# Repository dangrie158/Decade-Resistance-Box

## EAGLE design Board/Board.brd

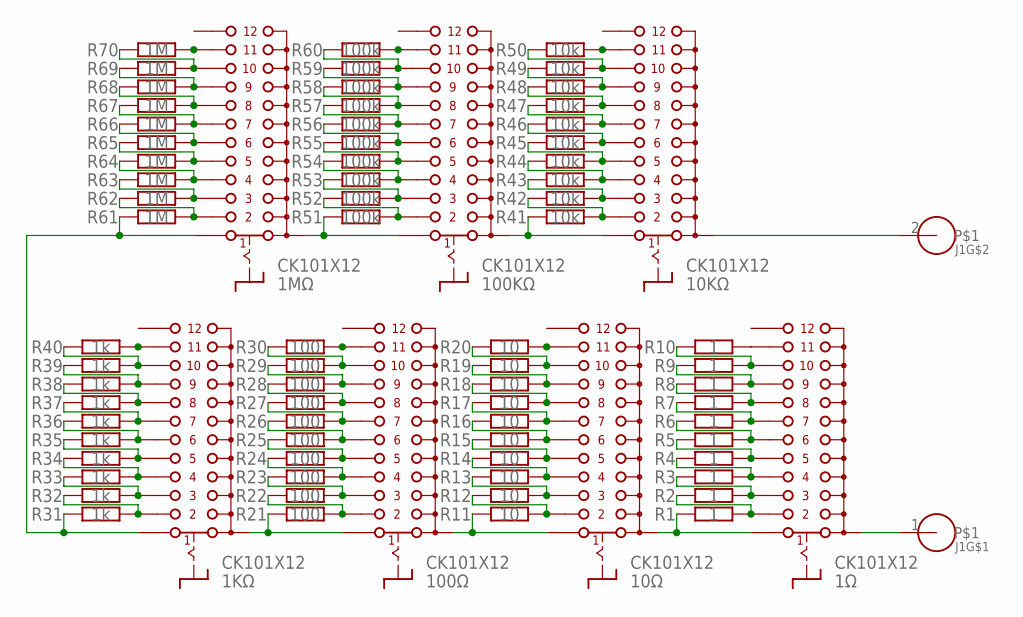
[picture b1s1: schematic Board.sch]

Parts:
1KΩ, 1MΩ, 1Ω, 10KΩ, 10Ω, 100KΩ, 100Ω: CK101X12
J1: MOLEX-1X2; MOLEX-1X2_LOCK
R1, R2, R3, R4, R5, R6, R7, R8, R9, R10: 1; 0207/2V
R11, R12, R13, R14, R15, R16, R17, R18, R19, R20: 10; 0207/2V
R21, R22, R23, R24, R25, R26, R27, R28, R29, R30: 100; 0207/2V
R31, R32, R33, R34, R35, R36, R37, R38, R39, R40: 1k; 0207/2V
R41, R42, R43, R44, R45, R46, R47, R48, R49, R50: 10k; 0207/2V
R51, R52, R53, R54, R55, R56, R57, R58, R59, R60: 100k; 0207/2V
R61, R62, R63, R64, R65, R66, R67, R68, R69, R70: 1M; 0207/2V

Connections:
unnamed: 1Ω.2, R1.2, R2.1
unnamed: 10Ω.2, R11.2, R12.1
unnamed: 10Ω.1, 100Ω.A, R11.1
unnamed: 10Ω.3, R12.2, R13.1
unnamed: 10Ω.4, R13.2, R14.1
unnamed: 10Ω.5, R14.2, R15.1
unnamed: 10Ω.6, R15.2, R16.1
unnamed: 10Ω.7, R16.2, R17.1
unnamed: 10Ω.8, R17.2, R18.1
unnamed: 10Ω.9, R18.2, R19.1
unnamed: 1KΩ.10, R39.2, R40.1
unnamed: 1Ω.3, R2.2, R3.1
unnamed: 1Ω.4, R3.2, R4.1
unnamed: 1Ω.5, R4.2, R5.1
unnamed: 1Ω.6, R5.2, R6.1
unnamed: 10Ω.10, R19.2, R20.1
unnamed: 1Ω.7, R6.2, R7.1
unnamed: 1Ω.8, R7.2, R8.1
unnamed: 1Ω.9, R8.2, R9.1
unnamed: 1Ω.10, R9.2, R10.1
unnamed: 1Ω.11, R10.2
unnamed: 10Ω.11, R20.2
unnamed: 100Ω.2, R21.2, R22.1
unnamed: 10KΩ.1, 100KΩ.A, R41.1
unnamed: 100Ω.3, R22.2, R23.1
unnamed: 100Ω.4, R23.2, R24.1
unnamed: 100Ω.5, R24.2, R25.1
unnamed: 100Ω.6, R25.2, R26.1
unnamed: 100Ω.7, R26.2, R27.1
unnamed: 100Ω.8, R27.2, R28.1
unnamed: 100Ω.9, R28.2, R29.1
unnamed: 100Ω.10, R29.2, R30.1
unnamed: 100Ω.11, R30.2
unnamed: 1KΩ.2, R31.2, R32.1
unnamed: 1Ω.1, 10Ω.A, R1.1
unnamed: 1KΩ.3, R32.2, R33.1
unnamed: 1KΩ.4, R33.2, R34.1
unnamed: 1KΩ.5, R34.2, R35.1
unnamed: 1KΩ.6, R35.2, R36.1
unnamed: 1KΩ.7, R36.2, R37.1
unnamed: 1KΩ.8, R37.2, R38.1
unnamed: 1KΩ.9, R38.2, R39.1
unnamed: 1KΩ.1, 1MΩ.1, R31.1, R61.1
unnamed: 1KΩ.11, R40.2
unnamed: 10KΩ.2, R41.2, R42.1
unnamed: 10KΩ.A, J1.2
unnamed: 10KΩ.3, R42.2, R43.1
unnamed: 10KΩ.4, R43.2, R44.1
unnamed: 10KΩ.5, R44.2, R45.1
unnamed: 10KΩ.6, R45.2, R46.1
unnamed: 10KΩ.7, R46.2, R47.1
unnamed: 10KΩ.8, R47.2, R48.1
unnamed: 10KΩ.9, R48.2, R49.1
unnamed: 10KΩ.10, R49.2, R50.1
unnamed: 10KΩ.11, R50.2
unnamed: 100KΩ.2, R51.2, R52.1
unnamed: 1MΩ.A, 100KΩ.1, R51.1
unnamed: 100KΩ.3, R52.2, R53.1
unnamed: 100KΩ.4, R53.2, R54.1
unnamed: 100KΩ.5, R54.2, R55.1
unnamed: 100KΩ.6, R55.2, R56.1
unnamed: 100KΩ.7, R56.2, R57.1
unnamed: 100KΩ.8, R57.2, R58.1
unnamed: 100KΩ.9, R58.2, R59.1
unnamed: 100KΩ.10, R59.2, R60.1
unnamed: 100KΩ.11, R60.2
unnamed: 1MΩ.2, R61.2, R62.1
unnamed: 1KΩ.A, 100Ω.1, R21.1
unnamed: 1MΩ.3, R62.2, R63.1
unnamed: 1MΩ.4, R63.2, R64.1
unnamed: 1MΩ.5, R64.2, R65.1
unnamed: 1MΩ.6, R65.2, R66.1
unnamed: 1MΩ.7, R66.2, R67.1
unnamed: 1MΩ.8, R67.2, R68.1
unnamed: 1MΩ.9, R68.2, R69.1
unnamed: 1MΩ.10, R69.2, R70.1
unnamed: 1MΩ.11, R70.2
unnamed: 1Ω.A, J1.1

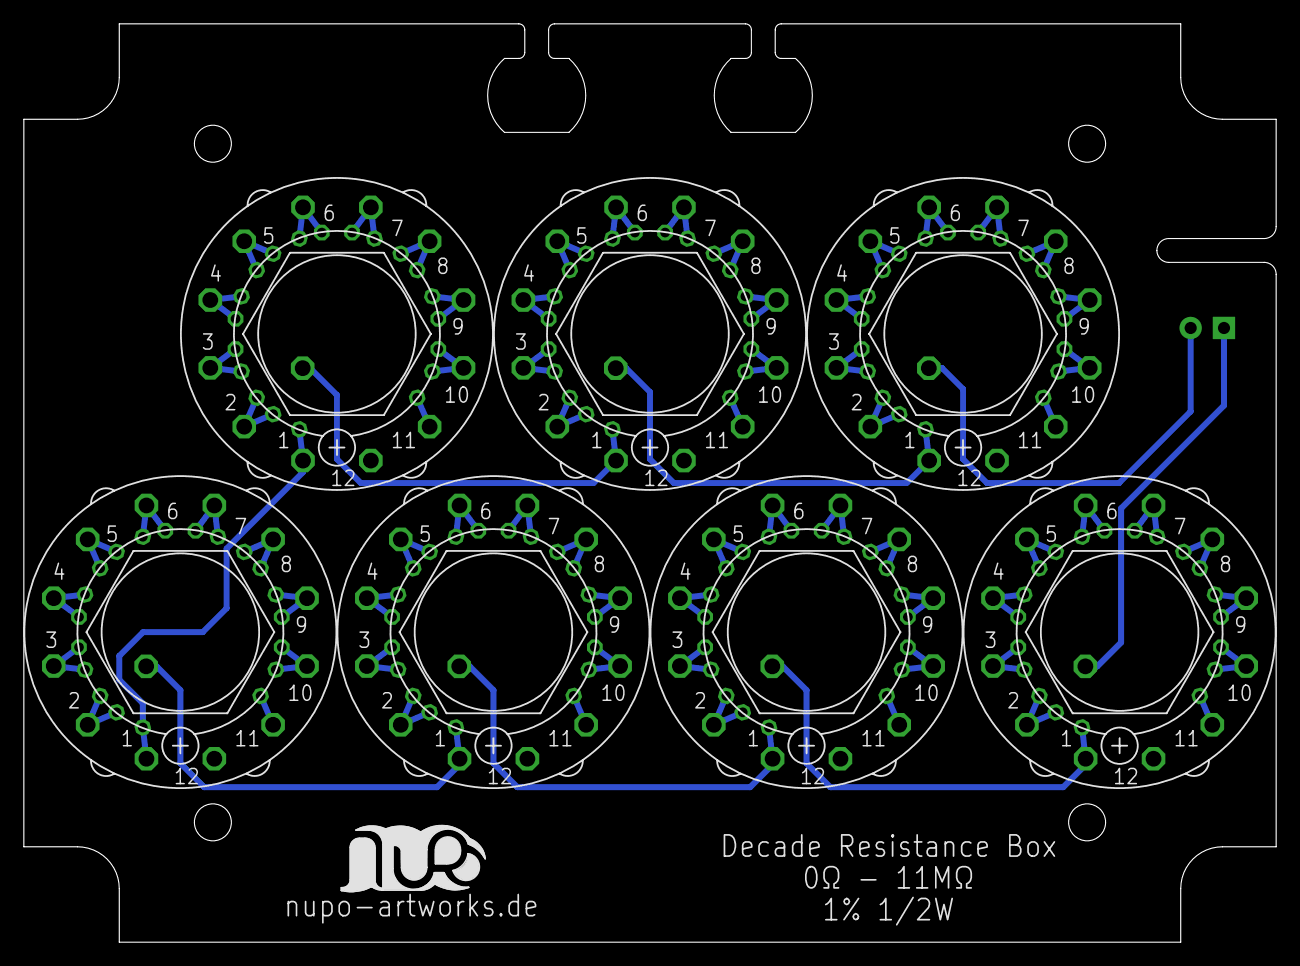
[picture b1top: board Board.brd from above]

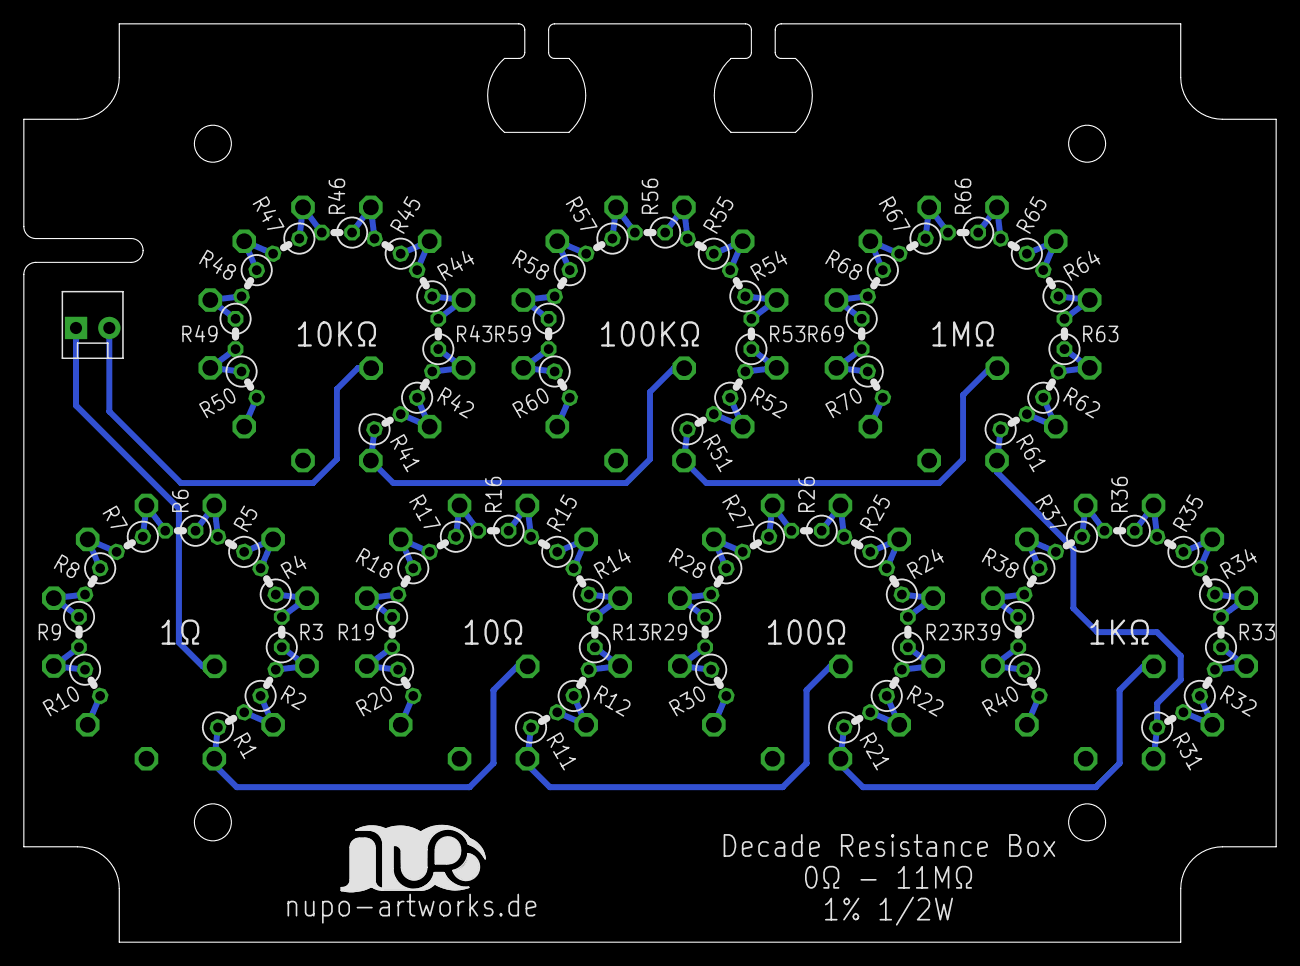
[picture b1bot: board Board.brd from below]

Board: 2 copper layers, 105.0 x 77.0 mm, 80 parts (72 on the bottom side), 78 nets.

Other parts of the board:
U$1, U$2: LOGO-SILKSCREEN

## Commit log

2019-01-03 added production gerbers
2019-01-03 moved board files to subfolder
2019-01-03 added Faceplate design file
2019-01-03 added script to calculate positions of the labels on the faceplate
2019-01-03 updated faceplate design
2019-01-03 added drawing exported from fusion for reference
2019-01-03 added PDF outputs for faceplate
2019-01-03 shortened shaft of rotary switch 3d model
2019-01-03 added first assembly render
2019-01-09 added PDF version of board and schematic
2019-01-09 updated Faceplate Layout
2019-01-10 removed open posiotion from faceplate for all dials except 1M
2019-01-10 added cutout file for faceplate
